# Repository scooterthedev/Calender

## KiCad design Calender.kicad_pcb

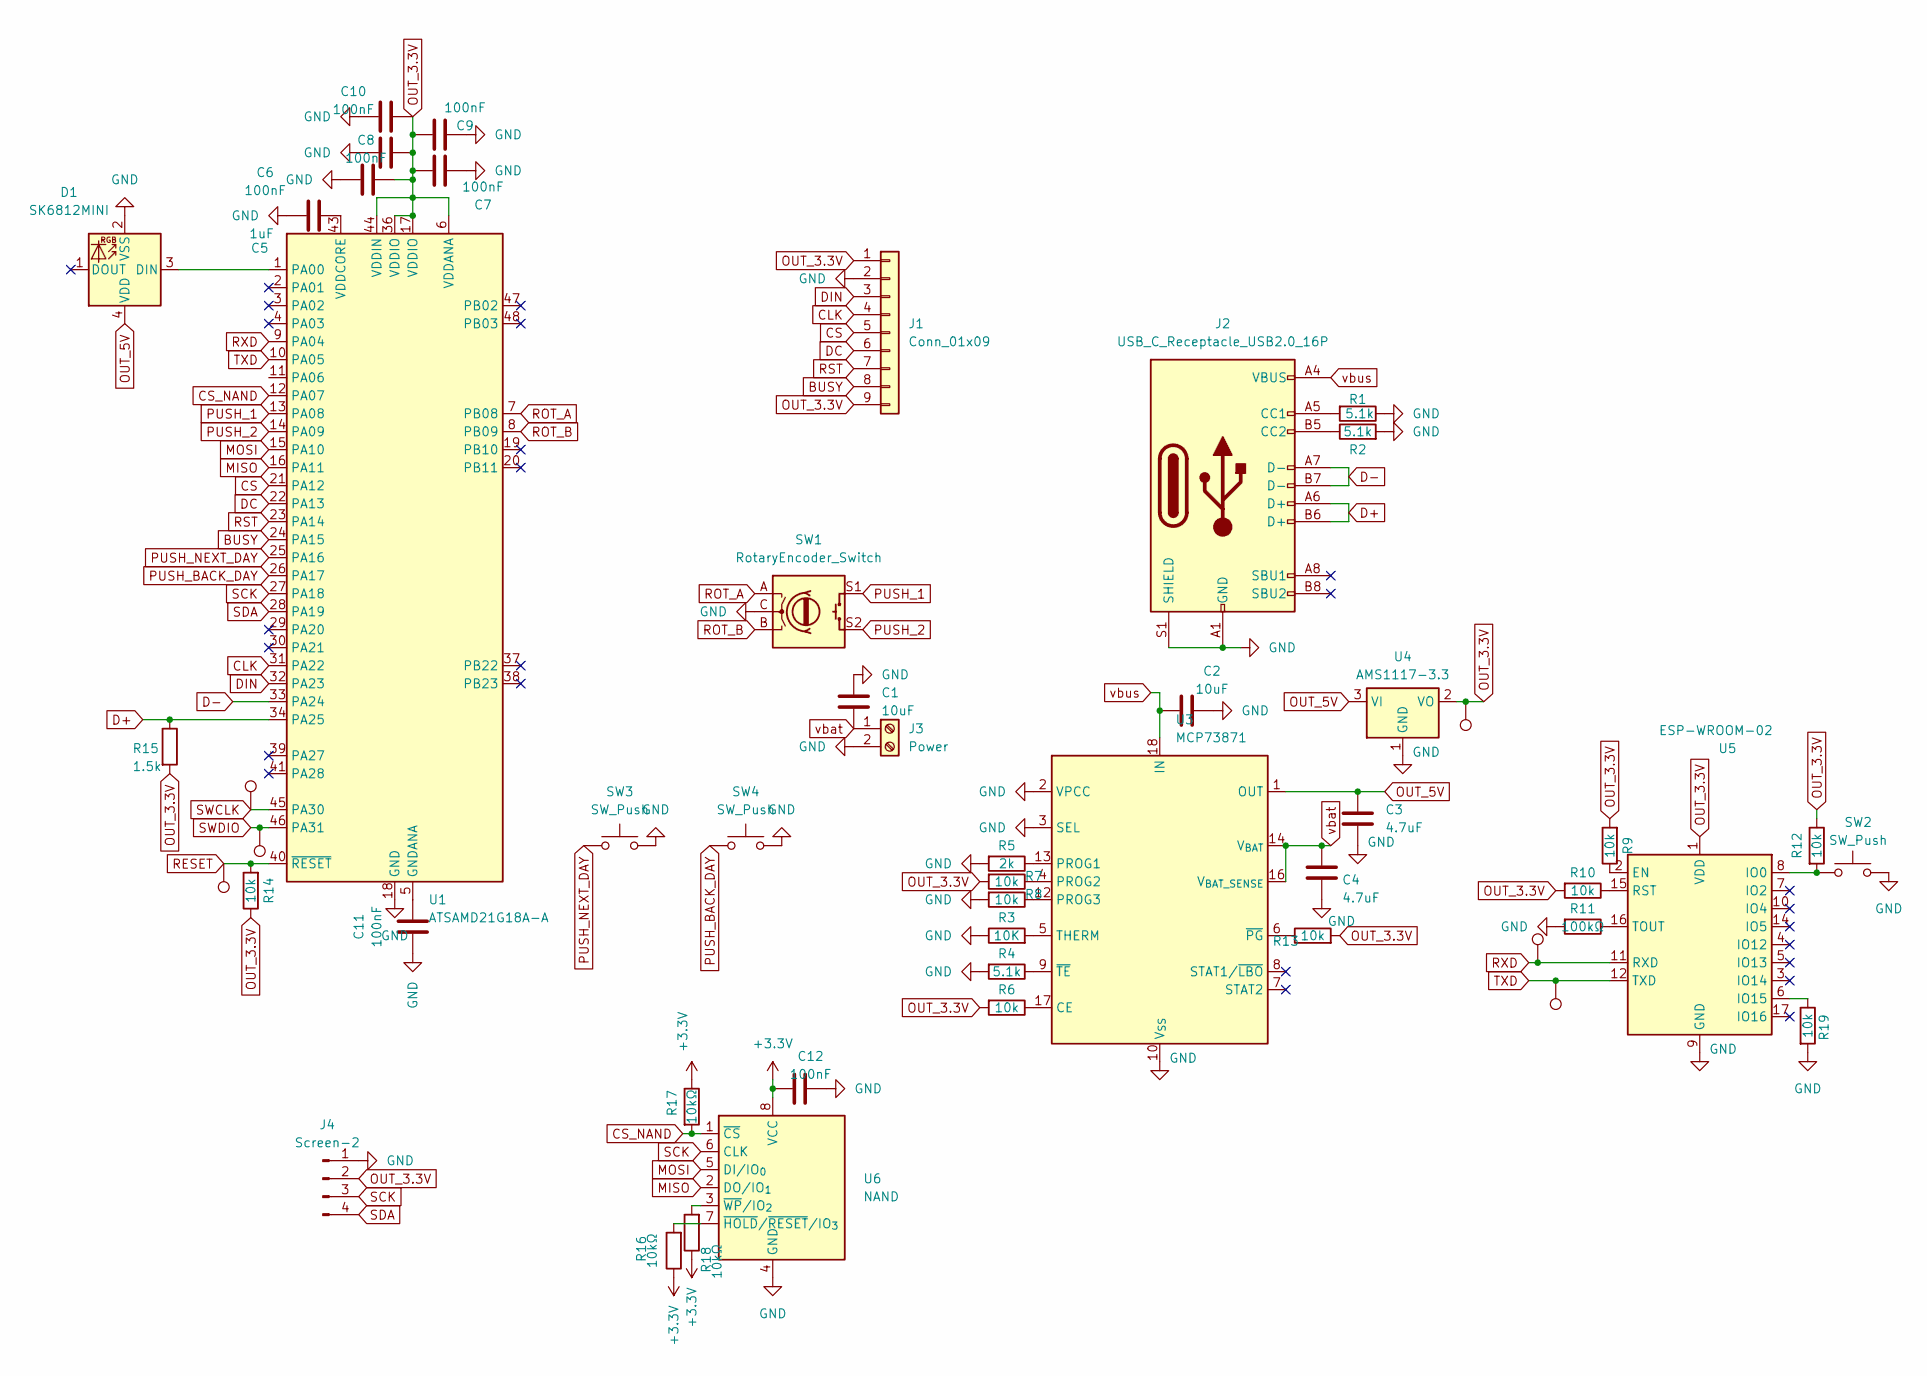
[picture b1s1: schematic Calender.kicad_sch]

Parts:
C1, C2: 10uF; C_0603_1608Metric
C3, C4: 4.7uF; C_0603_1608Metric
C5: 1uF; C_0603_1608Metric
C6, C7, C8, C9, C10, C11, C12: 100nF; C_0603_1608Metric
D1: SK6812MINI; LED_SK6812MINI_PLCC4_3.5x3.5mm_P1.75mm
J1: Conn_01x09; PinHeader_1x09_P1.00mm_Vertical
J2: USB_C_Receptacle_USB2.0_16P; USB_C_Receptacle_HCTL_HC-TYPE-C-16P-01A
J3: Power; TerminalBlock_bornier-2_P5.08mm
J4: Screen-2; PinHeader_1x04_P2.54mm_Vertical
R1, R2, R4: 5.1k; R_0603_1608Metric
R3: 10K; R_0603_1608Metric
R5: 2k; R_0603_1608Metric
R6, R7, R8, R9, R10, R12, R13, R14, R19: 10k; R_0603_1608Metric
R11: 100kΩ; R_0603_1608Metric
R15: 1.5k; R_0603_1608Metric
R16, R17, R18: 10kΩ; R_0603_1608Metric
SW1: RotaryEncoder_Switch; RotaryEncoder_Alps_EC11E-Switch_Vertical_H20mm
SW2, SW3, SW4: SW_Push; SW_PUSH_6mm
TP1, TP2, TP3, TP4, TP5, TP8: TestPoint; Pin_D1.0mm_L10.0mm_LooseFit
U1: ATSAMD21G18A-A; TQFP-48_7x7mm_P0.5mm
U3: MCP73871; QFN-20-1EP_4x4mm_P0.5mm_EP2.5x2.5mm
U4: AMS1117-3.3; SOT-223-3_TabPin2
U5: ESP-WROOM-02
U6: NAND; SOIC-8_5.3x5.3mm_P1.27mm

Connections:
+3.3V: C12.1, R16.1, R17.1, R18.1, U6.8 (VCC)
BUSY: J1.8, U1.24 (PA15)
CLK: J1.4, U1.31 (PA22)
CS: J1.5, U1.21 (PA12)
CS_NAND: R17.2, U1.12 (PA07), U6.1 (~CS)
D+: J2.A6 (D+), J2.B6 (D+), R15.1, U1.34 (PA25)
D-: J2.A7 (D-), J2.B7 (D-), U1.33 (PA24)
DC: J1.6, U1.22 (PA13)
DIN: J1.3, U1.32 (PA23)
GND: C1.1, C2.2, C3.2, C4.2, C5.2, C6.2, C7.2, C8.2, C9.2, C10.2, C11.2, C12.2, D1.2 (VSS), J1.2, J2.A1 (GND), J2.A12 (GND), J2.B1 (GND), J2.B12 (GND), J2.S1 (SHIELD), J3.2, J4.1, R1.1, R2.2, R3.1, R4.2, R5.2, R8.2, R11.2, R19.2, SW1.C, SW2.2, SW3.2, SW4.2, U1.18 (GND), U1.35 (GND), U1.42 (GND), U3.2 (VPCC), U3.3 (SEL), U3.10 (V_{SS}), U3.11 (V_{SS}), U3.21 (V_{SS}), U4.1 (GND), U5.9 (GND), U5.13 (GND), U5.18 (GND), U5.19 (GND), U6.4 (GND)
MISO: U1.16 (PA11), U6.2 (DO/IO_{1})
MOSI: U1.15 (PA10), U6.5 (DI/IO_{0})
unnamed: D1.3 (DIN), U1.1 (PA00)
unnamed: J2.A5 (CC1), R1.2
unnamed: J2.B5 (CC2), R2.1
unnamed: C11.1, U1.5 (GNDANA)
unnamed: C5.1, U1.43 (VDDCORE)
unnamed: R6.1, U3.17 (CE)
unnamed: R5.1, U3.13 (PROG1)
unnamed: R7.1, U3.4 (PROG2)
unnamed: R8.1, U3.12 (PROG3)
unnamed: R3.2, U3.5 (THERM)
unnamed: R13.1, U3.6 (~PG)
unnamed: R4.1, U3.9 (~TE)
unnamed: R9.1, U5.2 (EN)
unnamed: R12.2, SW2.1, U5.8 (IO0)
unnamed: R19.1, U5.6 (IO15)
unnamed: R10.1, U5.15 (RST)
unnamed: R11.1, U5.16 (TOUT)
unnamed: R16.2, U6.7 (~HOLD/~RESET/IO_{3})
unnamed: R18.2, U6.3 (~WP/IO_{2})
OUT_3.3V: C6.1, C7.1, C8.1, C9.1, C10.1, J1.1, J1.9, J4.2, R6.2, R7.2, R9.2, R10.2, R12.1, R13.2, R14.1, R15.2, TP8.1, U1.6 (VDDANA), U1.17 (VDDIO), U1.36 (VDDIO), U1.44 (VDDIN), U4.2 (VO), U5.1 (VDD)
OUT_5V: C3.1, D1.4 (VDD), U3.1 (OUT), U3.20 (OUT), U4.3 (VI)
PUSH_1: SW1.S1, U1.13 (PA08)
PUSH_2: SW1.S2, U1.14 (PA09)
PUSH_BACK_DAY: SW4.1, U1.26 (PA17)
PUSH_NEXT_DAY: SW3.1, U1.25 (PA16)
RESET: R14.2, TP3.1, U1.40 (~RESET)
ROT_A: SW1.A, U1.7 (PB08)
ROT_B: SW1.B, U1.8 (PB09)
RST: J1.7, U1.23 (PA14)
RXD: TP2.1, U1.9 (PA04), U5.11 (RXD)
SCK: J4.3, U1.27 (PA18), U6.6 (CLK)
SDA: J4.4, U1.28 (PA19)
SWCLK: TP5.1, U1.45 (PA30)
SWDIO: TP4.1, U1.46 (PA31)
TXD: TP1.1, U1.10 (PA05), U5.12 (TXD)
vbat: C1.2, C4.1, J3.1, U3.14 (V_{BAT}), U3.15 (V_{BAT}), U3.16 (V_{BAT_SENSE})
vbus: C2.1, J2.A4 (VBUS), J2.A9 (VBUS), J2.B4 (VBUS), J2.B9 (VBUS), U3.18 (IN), U3.19 (IN)

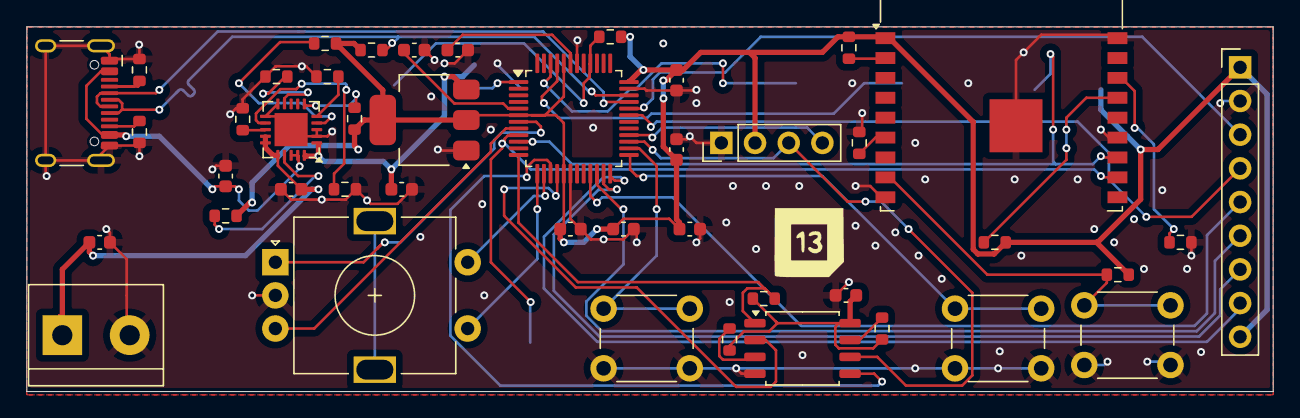
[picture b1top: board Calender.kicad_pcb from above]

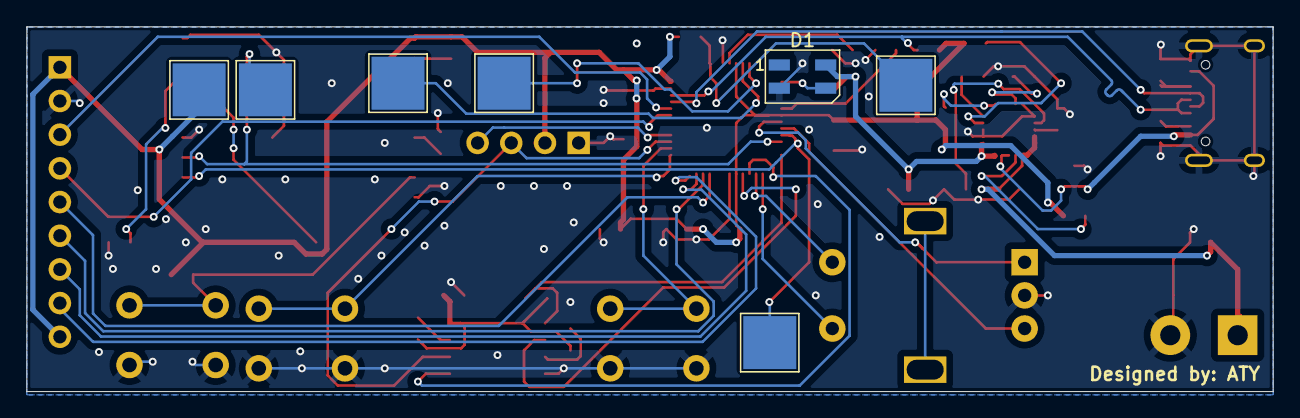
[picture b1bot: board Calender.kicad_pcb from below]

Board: 2 copper layers, 94.0 x 27.5 mm, 51 parts (7 on the bottom side), 49 nets.

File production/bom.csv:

Designator,Footprint,Quantity,Value,LCSC Part #
"C1, C2",0603,2,10uF,
"C10, C11, C12, C6, C7, C8, C9",0603,7,100nF,
"C3, C4",0603,2,4.7uF,
C5,0603,1,1uF,
D1,LED_SK6812MINI_PLCC4_3.5x3.5mm_P1.75mm,1,SK6812MINI,
J1,PinHeader_1x09_P2.54mm_Vertical,1,Conn_01x09,
J2,USB_C_Receptacle_HCTL_HC-TYPE-C-16P-01A,1,USB_C_Receptacle_USB2.0_16P,
J3,TerminalBlock_bornier-2_P5.08mm,1,Power,
J4,PinHeader_1x04_P2.54mm_Vertical,1,Screen-2,
"R1, R2, R4",0603,3,5.1k,
"R10, R12, R13, R14, R19, R3, R6, R7, R8, R9",0603,10,10k,
R11,0603,1,100kΩ,
R15,0603,1,1.5k,
"R16, R17, R18",0603,3,10kΩ,
R5,0603,1,2k,
SW1,RotaryEncoder_Alps_EC11E-Switch_Vertical_H20mm,1,RotaryEncoder_Switch,
"SW2, SW3, SW4",SW_PUSH_6mm,3,SW_Push,
"TP1, TP2, TP3, TP4, TP5, TP8",TestPoint_Pad_4.0x4.0mm,6,TestPoint,
U1,TQFP-48_7x7mm_P0.5mm,1,ATSAMD21G18A-A,
U3,QFN-20-1EP_4x4mm_P0.5mm_EP2.5x2.5mm,1,MCP73871,
U4,SOT-223-3_TabPin2,1,AMS1117-3.3,
U5,ESP-WROOM-02,1,ESP-WROOM-02,
U6,SOIC-8_5.3x5.3mm_P1.27mm,1,NAND,

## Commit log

2025-08-27 Fixed the stupid PCB, and added prod files
2025-08-27 one more time
2025-08-27 fixed the esp32
2025-08-27 final version
